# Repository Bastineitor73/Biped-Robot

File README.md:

# Contacto

Quieres ser parte de B1P0? Envía un correo a josespi@udec.cl, mariomedina@udec.cl, agarrido2018@udec.cl o ginostroza2020@udec.cl

# Contenidos
- [Proyecto B1P0](#proyecto-b1p0)
  * [Objetivo](#objetivo)
  * [Visiones](#visiones)
  * [Temas actuales](#temas-actuales)
  * [Diagrama Electrico](#diagrama-electrico)
- [Avances](#avances)
- [Invitacion Charla](#invitacion-charla)
- [Contacto](#contacto)

# Proyecto B1P0

Quieres ser parte de B1P0? Envía un correo a agarrido2018@udec.cl o a ginostroza2020@udec.cl

## Objetivo
"Crear un robot bípedo estable y escalable a lo largo del tiempo desarrollado por alumnos del DIE, capaz de desenvolverse en entornos industriales complejos, catástrofes naturales, inspecciones y escenarios de alto riesgo humano"

## Visiones

## Temas actuales
1.- Modelación física y desarrollo de un gemelo digital para entrenamiento y simulaciones

2.- Rediseño estructural del robot bípedo existente, mediante análisis de esfuerzos, estudio de materiales, mejoras en sistemas mecánicos y resistencia.

3.- Diseño e integración de una arquitectura de software basada en ROS/ROS2 para la comunicación entre CPU, microcontroladores, actuadores y usuario

4.- Diseño e implementación de un sistema de control remoto inalámbrico utilizando tecnologías RF, WiFi o Bluetooth.

5.- Diseño e implementación de un sistema de control adaptativo o predictivo para la estabilidad del robot bípedo

6.- Desarrollo de un sistema de estimación de estados mediante fusión de datos inerciales (IMU) y modelos dinámicos

7.- Implementación de un sistema de percepción visual y mapeo de entorno mediante cámara de profundidad

# Avance Actual

## Octubre 2025

https://github.com/user-attachments/assets/e0c73ede-dcd1-4829-920c-aed435cbe2b3

# Revisa nuestra Charla

https://www.canva.com/design/DAG2QE-IAb0/ETZ7DED0be4jHASCjCmeyw/view?utm_content=DAG2QE-IAb0&utm_campaign=designshare&utm_medium=link2&utm_source=uniquelinks&utlId=h5e711771e6

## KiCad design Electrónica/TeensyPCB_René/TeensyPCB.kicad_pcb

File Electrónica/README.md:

# Diagrama Electrico

# Lista de Dispositivos

## Microcontrolador Teensy 4.1

## SparkFun OpenLog Artemis

## Raspberry Pi 5, 16 GB RAM

## Cámara Intel RealSense D435i

## Batería Lipo
- 22.2V
- 6 celdas
- 5000 mAh

# Desarollo PCB's
Interacción de los componentes

## Monitor de bateria y Medidor de combustible
- Monitor MP2790
- Fuel Gauge MPF42795
- Comunicacion por I2C con librería "MP27XX.h"

- Placa accesoria para llave de paso MOS

- Placa accesoria UI Medidor de combustible

## Placa de alimentacion
- Conversor buck TPS54531 5V @25W
- Regulador lineal TLV757p 3V3 @3W

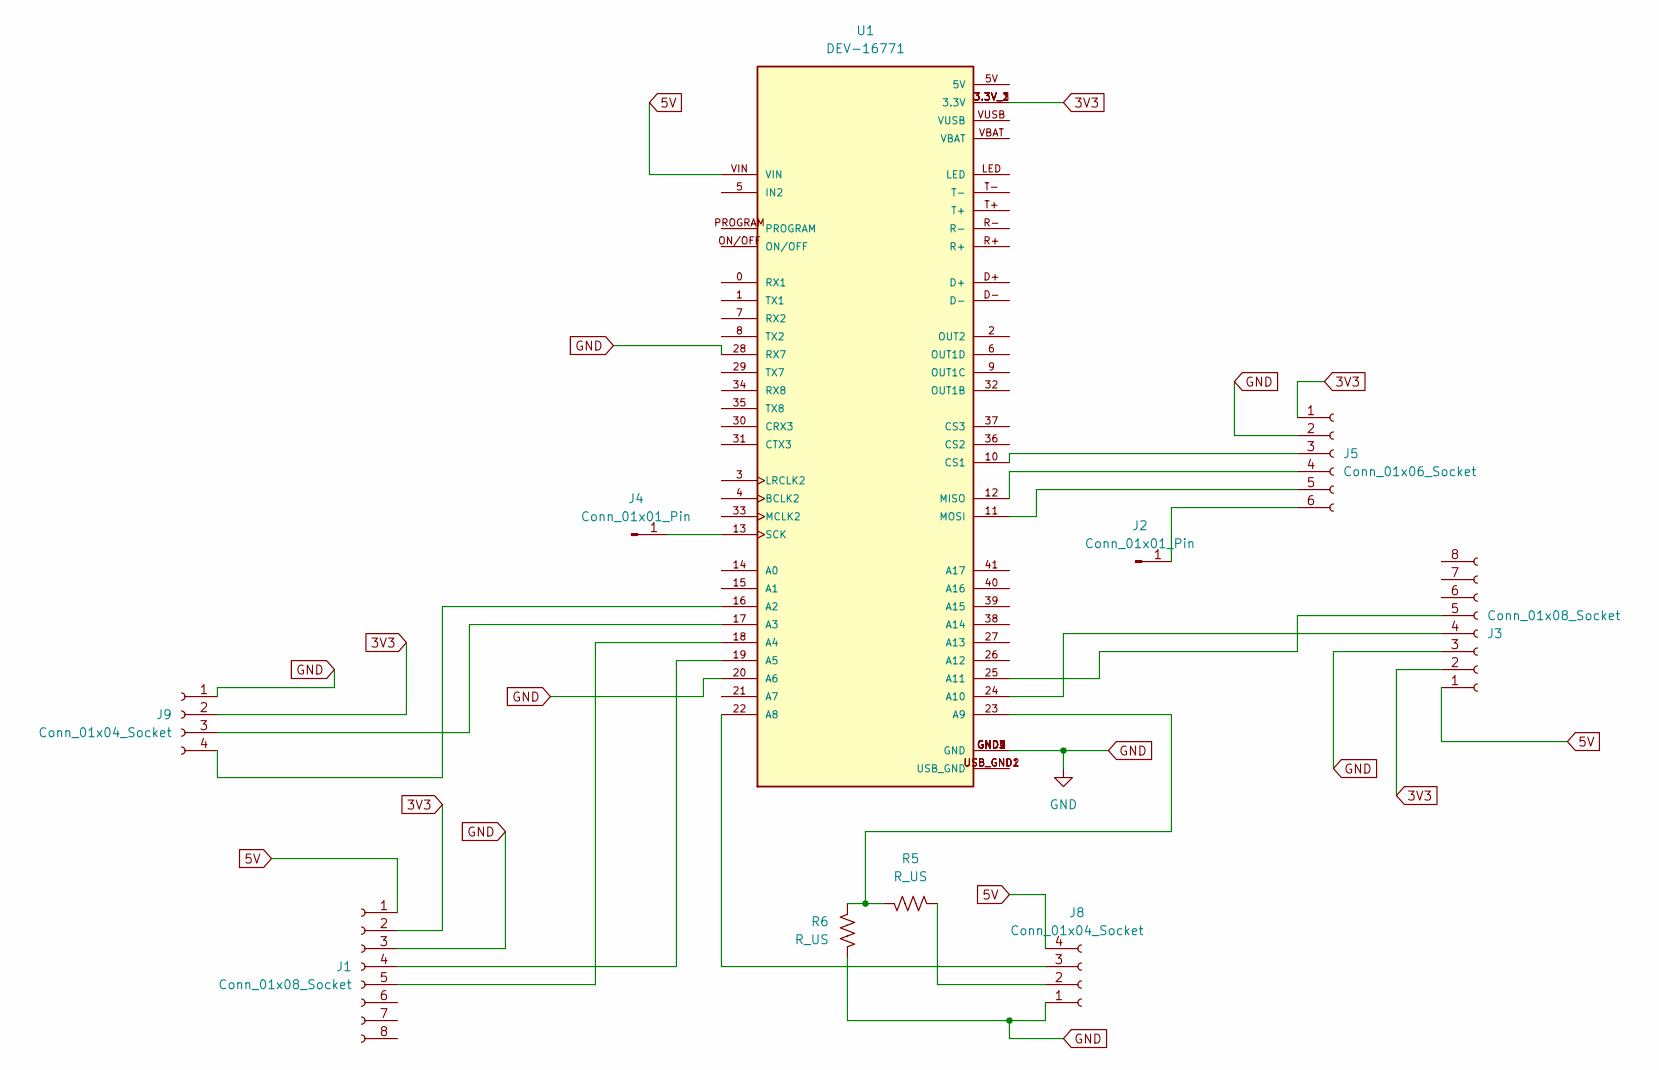
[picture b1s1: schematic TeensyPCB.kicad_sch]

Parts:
J1, J3: Conn_01x08_Socket; PinHeader_1x08_P2.54mm_Vertical
J2, J4: Conn_01x01_Pin; PinHeader_1x01_P2.54mm_Vertical
J5: Conn_01x06_Socket; PinHeader_1x06_P2.54mm_Vertical
J8, J9: Conn_01x04_Socket; PinHeader_1x04_P2.54mm_Vertical
R5, R6: R_US; R_Axial_DIN0207_L6.3mm_D2.5mm_P10.16mm_Horizontal
U1: DEV-16771; MODULE_DEV-16771; PARTREV 4.1

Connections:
3V3: J1.2, J3.2, J5.1, J9.2, U1.3.3V_1 (3.3V), U1.3.3V_2 (3.3V), U1.3.3V_3 (3.3V)
5V: J1.1, J3.1, J8.4, U1.VIN
GND: J1.3, J3.3, J5.2, J8.1, J9.1, R6.2, U1.20 (A6), U1.28 (RX7), U1.GND1 (GND), U1.GND2 (GND), U1.GND3 (GND), U1.GND4 (GND), U1.GND5 (GND)
unnamed: J1.4, U1.19 (A5)
unnamed: J1.5, U1.18 (A4)
unnamed: J2.1, J5.6
unnamed: J3.4, U1.24 (A10)
unnamed: J3.5, U1.25 (A11)
unnamed: J4.1, U1.13 (SCK)
unnamed: J5.3, U1.10 (CS1)
unnamed: J5.4, U1.12 (MISO)
unnamed: J5.5, U1.11 (MOSI)
unnamed: J8.2, R5.1
unnamed: J8.3, U1.22 (A8)
unnamed: J9.3, U1.17 (A3)
unnamed: J9.4, U1.16 (A2)
unnamed: R5.2, R6.1, U1.23 (A9)
unnamed: U1.USB_GND1 (USB_GND), U1.USB_GND2 (USB_GND)

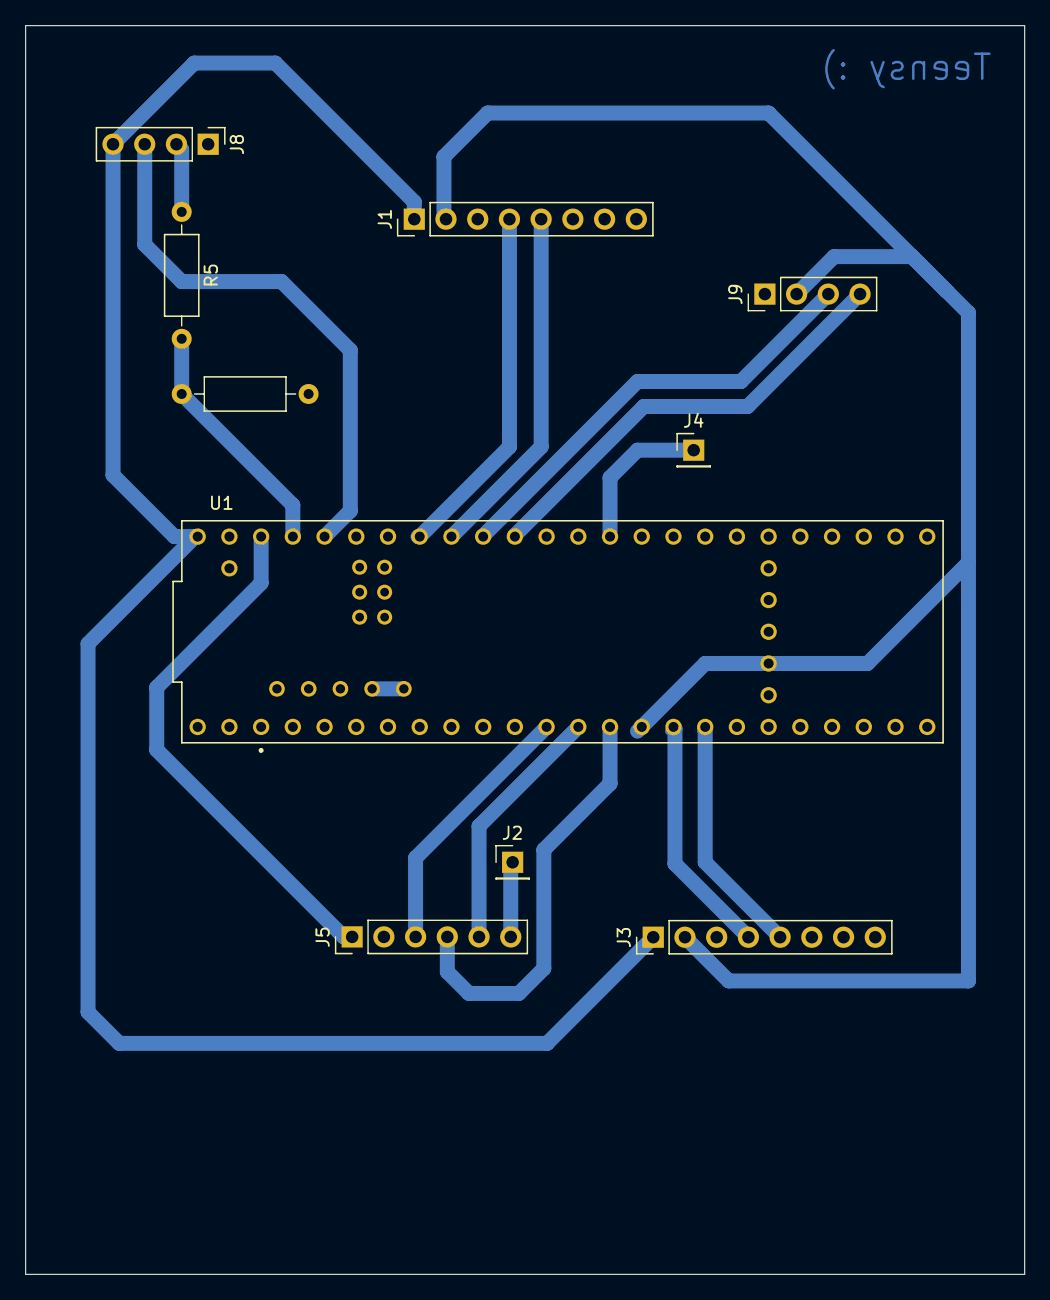
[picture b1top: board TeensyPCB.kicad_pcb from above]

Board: 2 copper layers, 80.0 x 100.0 mm, 10 parts (0 on the bottom side), 18 nets.

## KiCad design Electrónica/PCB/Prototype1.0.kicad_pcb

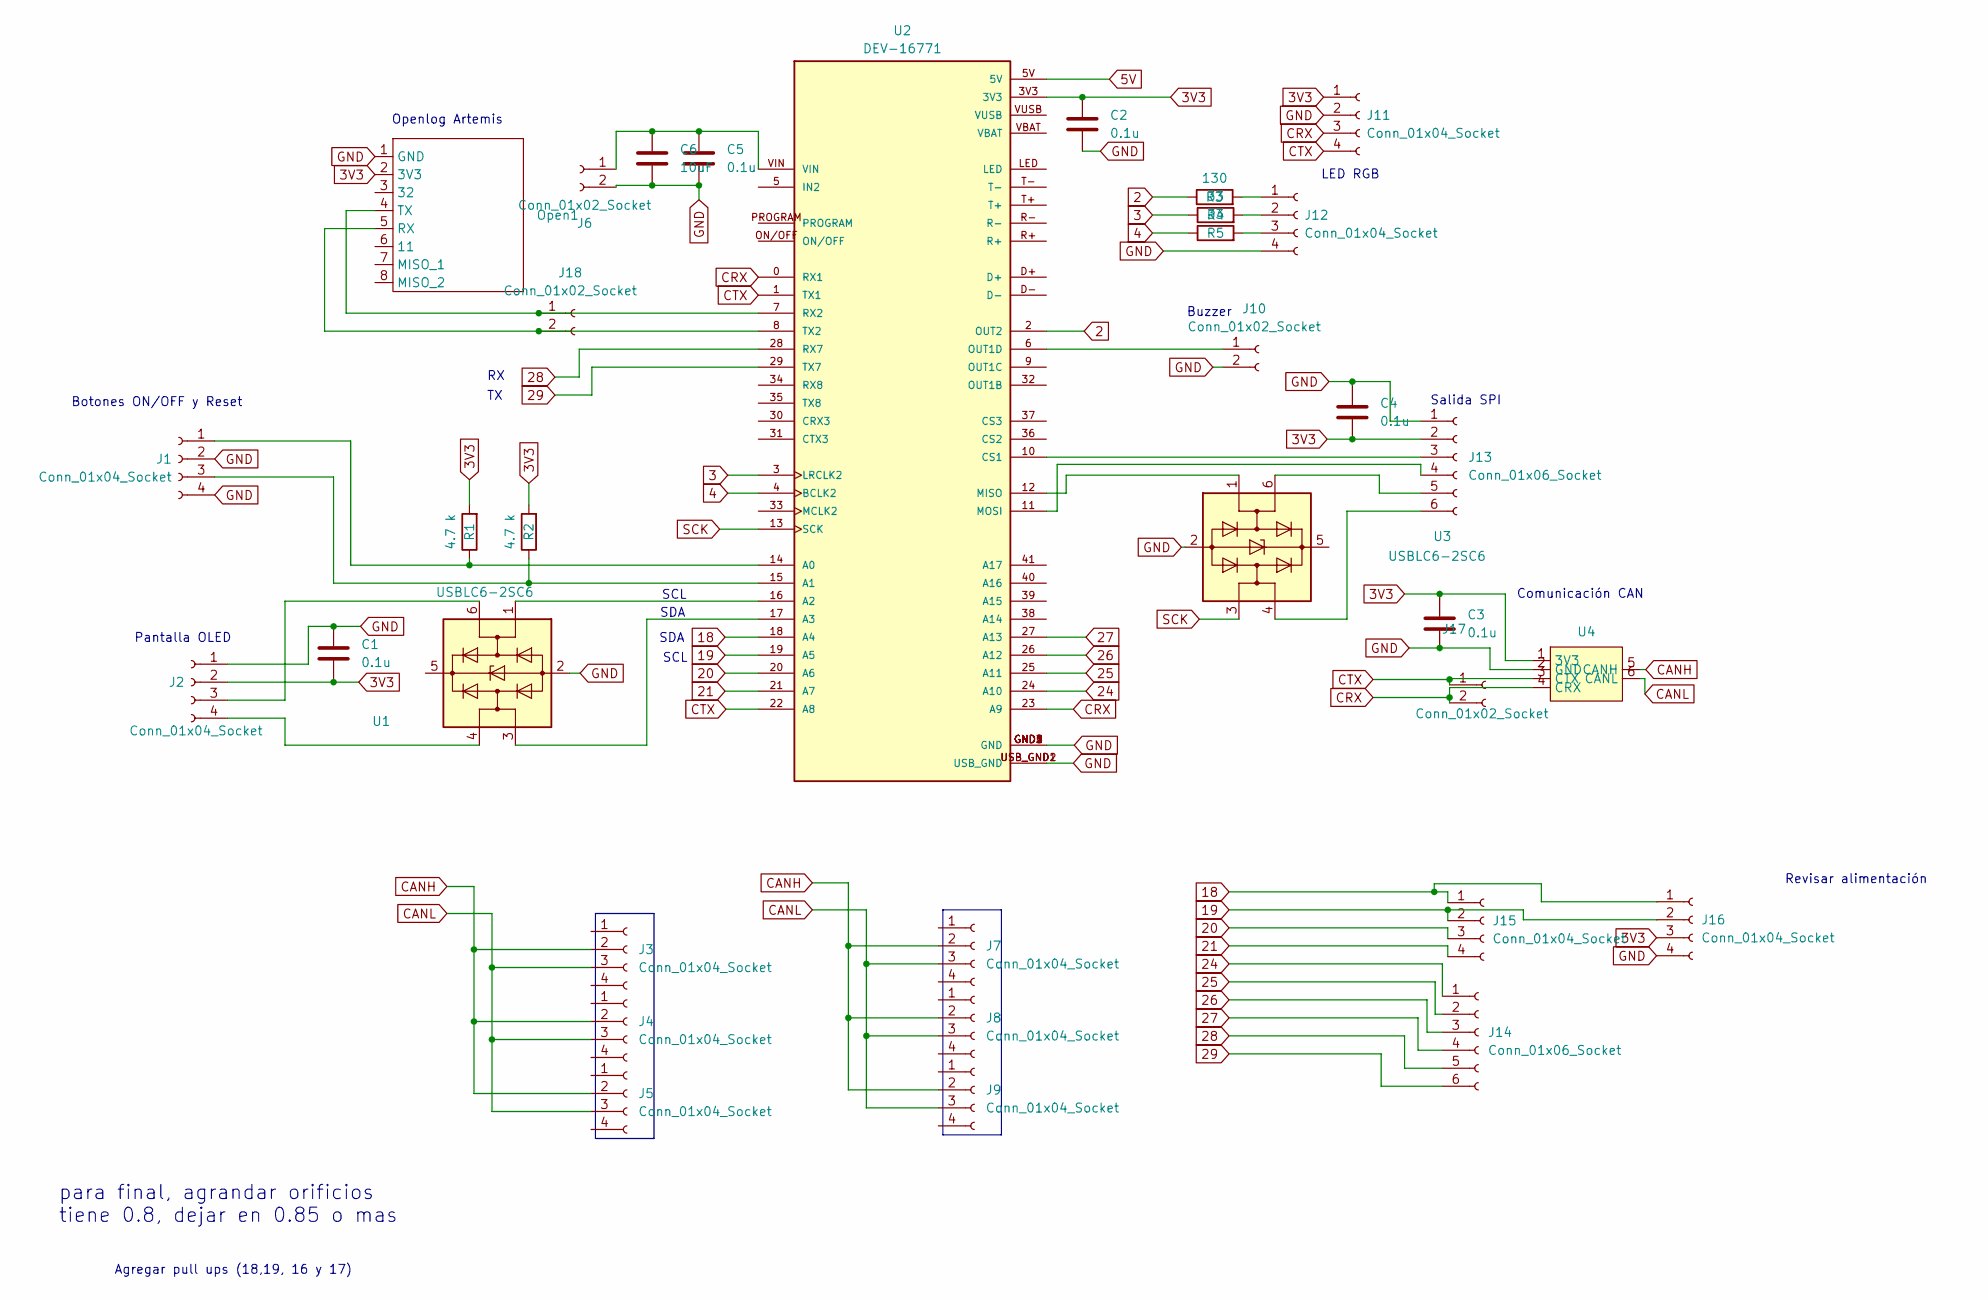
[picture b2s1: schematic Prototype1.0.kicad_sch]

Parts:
C1, C2, C3, C4, C5: 0.1u; C_0805_2012Metric_Pad1.18x1.45mm_HandSolder
C6: 10uF; C_0805_2012Metric_Pad1.18x1.45mm_HandSolder
J1, J2, J11, J12, J15, J16: Conn_01x04_Socket; PinSocket_1x04_P2.54mm_Vertical
J3, J4, J5, J7, J8, J9: Conn_01x04_Socket; JST_GH_SM04B-GHS-TB_1x04-1MP_P1.25mm_Horizontal
J6: Conn_01x02_Socket; TerminalBlock_Phoenix_MKDS-1,5-2-5.08_1x02_P5.08mm_Horizont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
J10, J17, J18: Conn_01x02_Socket; PinSocket_1x02_P2.54mm_Vertical
J13, J14: Conn_01x06_Socket; PinSocket_1x06_P2.54mm_Vertical
Open1: Openlog Artemis
R1, R2: 4.7 k; R_0805_2012Metric_Pad1.20x1.40mm_HandSolder
R3: 130; R_0805_2012Metric_Pad1.20x1.40mm_HandSolder
R4, R5: 33; R_0805_2012Metric_Pad1.20x1.40mm_HandSolder
U1, U3: USBLC6-2SC6; SOT-23-6
U2: DEV-16771; MODULE_DEV-16771; PARTREV 4.1
U4: ModuloCan

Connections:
2: R3.1, U2.2 (OUT2)
3: R4.1, U2.3 (LRCLK2)
3V3: C1.2, C2.1, C3.1, C4.2, J2.2, J11.1, J13.2, J16.3, Open1.2 (3V3), R1.2, R2.2, U2.3V3, U4.1 (3V3)
4: R5.1, U2.4 (BCLK2)
5V: U2.5V
18: J15.1, J16.1, U2.18 (A4)
19: J15.2, J16.2, U2.19 (A5)
20: J15.3, U2.20 (A6)
21: J15.4, U2.21 (A7)
24: J14.1, U2.24 (A10)
25: J14.2, U2.25 (A11)
26: J14.3, U2.26 (A12)
27: J14.4, U2.27 (A13)
28: J14.5, U2.28 (RX7)
29: J14.6, U2.29 (TX7)
CANH: J3.2, J4.2, J5.2, J7.2, J8.2, J9.2, U4.5 (CANH)
CANL: J3.3, J4.3, J5.3, J7.3, J8.3, J9.3, U4.6 (CANL)
CRX: J11.3, J17.2, U2.0 (RX1), U2.23 (A9), U4.4 (CRX)
CTX: J11.4, J17.1, U2.1 (TX1), U2.22 (A8), U4.3 (CTX)
GND: C1.1, C2.2, C3.2, C4.1, C5.2, C6.2, J1.2, J1.4, J2.1, J6.2, J10.2, J11.2, J12.4, J13.1, J16.4, Open1.1 (GND), U1.2 (GND), U2.GND1 (GND), U2.GND2 (GND), U2.GND3 (GND), U2.GND4 (GND), U2.GND5 (GND), U2.USB_GND1 (USB_GND), U2.USB_GND2 (USB_GND), U3.2 (GND), U4.2 (GND)
unnamed: J1.1, R1.1, U2.14 (A0)
unnamed: J1.3, R2.1, U2.15 (A1)
unnamed: J2.3, U1.6 (I/O1)
unnamed: J2.4, U1.4 (I/O2)
unnamed: C5.1, C6.1, J6.1, U2.VIN
unnamed: J10.1, U2.6 (OUT1D)
unnamed: J12.1, R3.2
unnamed: J12.2, R4.2
unnamed: J12.3, R5.2
unnamed: J13.3, U2.10 (CS1)
unnamed: J13.4, U2.11 (MOSI)
unnamed: J13.5, U3.6 (I/O1)
unnamed: J13.6, U3.4 (I/O2)
unnamed: J18.1, Open1.4 (TX), U2.7 (RX2)
unnamed: J18.2, Open1.5 (RX), U2.8 (TX2)
unnamed: U1.1 (I/O1), U2.16 (A2)
unnamed: U1.3 (I/O2), U2.17 (A3)
unnamed: U2.12 (MISO), U3.1 (I/O1)
SCK: U2.13 (SCK), U3.3 (I/O2)

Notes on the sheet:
Botones ON/OFF y Reset
SDA
Agregar pull ups (18,19, 16 y 17)
SCL
Buzzer
Comunicación CAN
Salida SPI
Revisar alimentación
LED RGB
para final, agrandar orificios tiene 0.8, dejar en 0.85 o mas
Openlog Artemis
Pantalla OLED

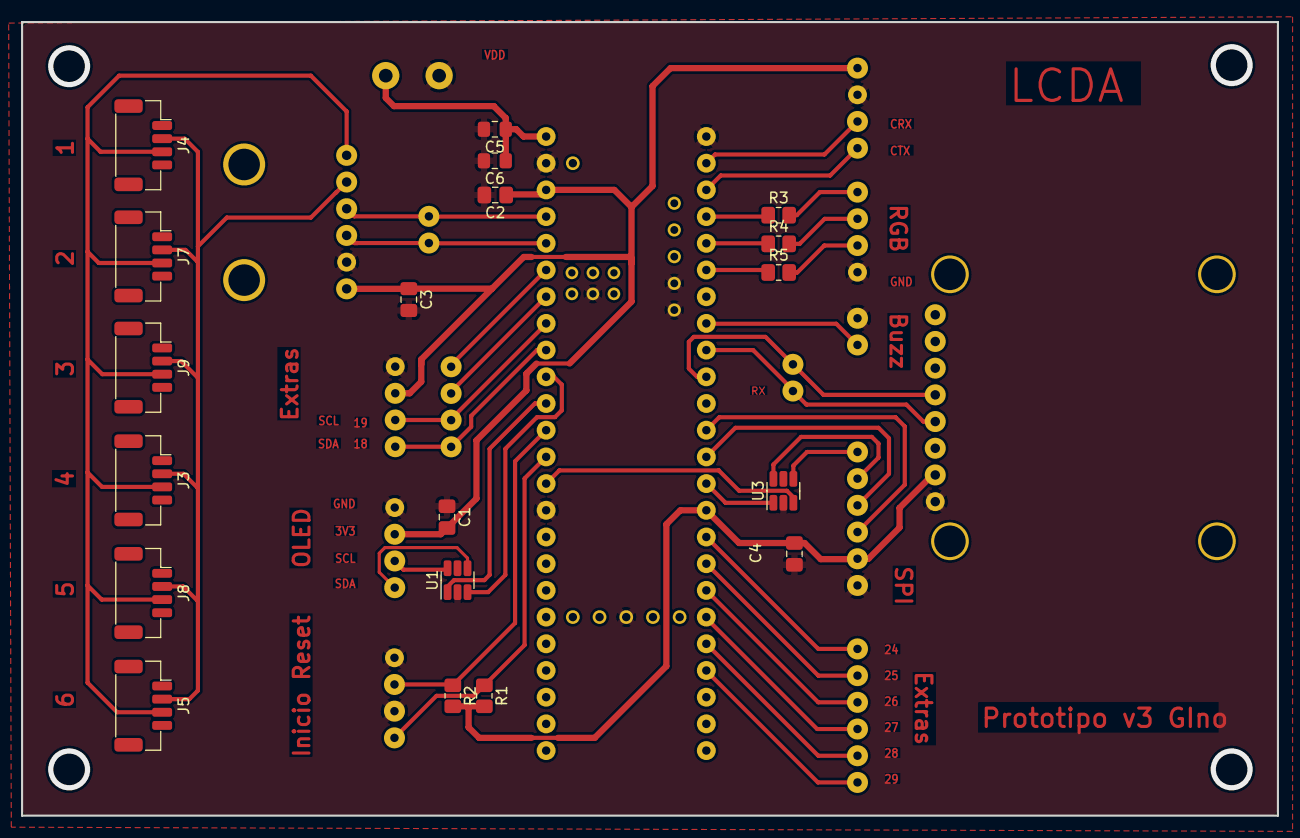
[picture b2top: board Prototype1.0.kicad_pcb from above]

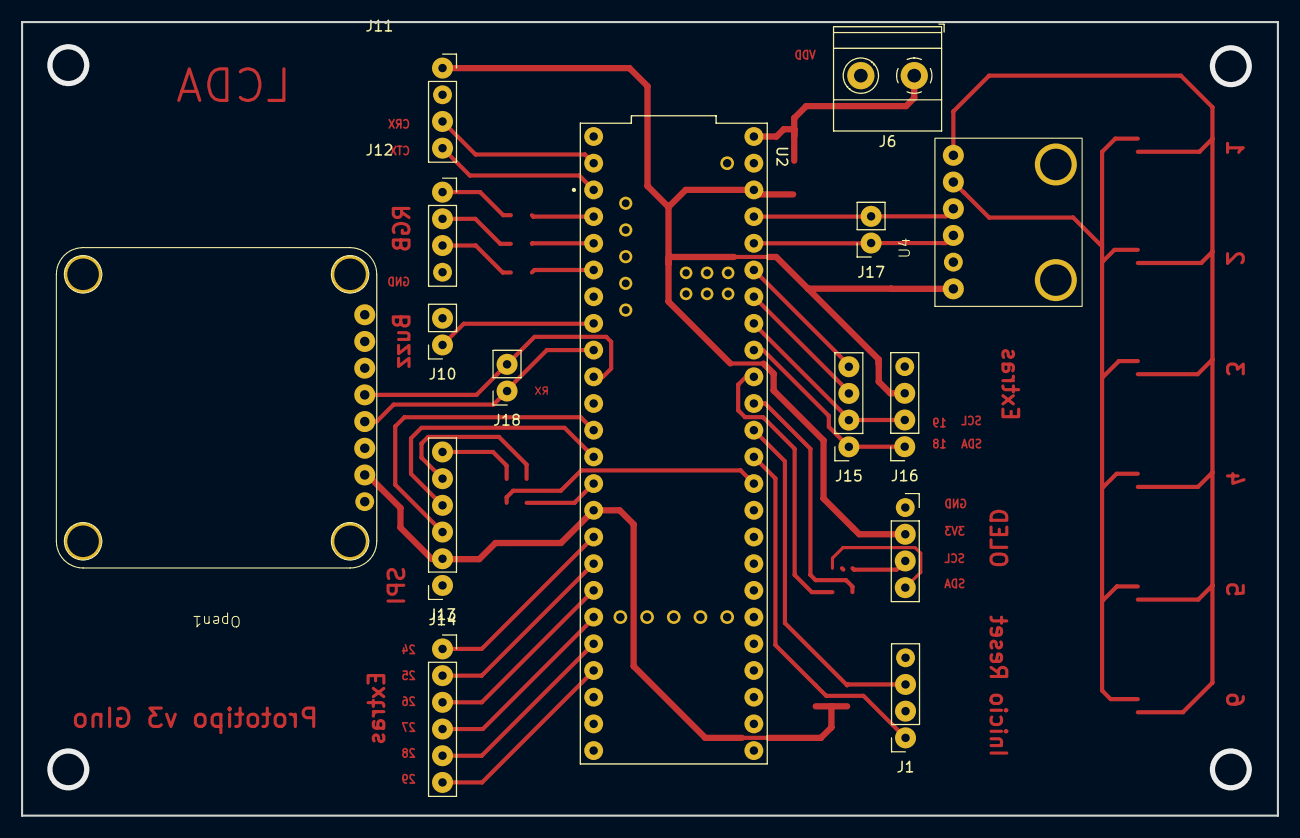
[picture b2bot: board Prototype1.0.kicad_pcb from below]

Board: 2 copper layers, 119.5 x 75.5 mm, 34 parts (15 on the bottom side), 38 nets.

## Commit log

2024-11-16 Create Papers
2025-04-05 Create aaaaa
2025-04-14 Create TeensyPCB_René
2025-04-14 Create aaa
2025-04-14 Rename Informe Final PELN Bastián.pdf to Actuadores Eléctricos Propioceptivos.pdf
2025-04-15 Agrego tabla de ensayos del motor
2025-07-23 Prototype1.0
2025-07-23 Create Fotos
2025-08-14 Esquema placas y software
2025-08-14 Rename PCB_MP2790png.png to PCB_MP2790.png
2025-08-14 Update README.md
    agregando placas alonso
2025-08-14 Subiendo libreria MP2790 alpha
    Para comunicarse con monitor de bateria
2025-08-14 resumen clase mp2790
2025-08-17 Actualizando rutina principal
2025-08-25 Adjust image dimensions in README.md
2025-08-25 Adjust image sizes in README.md
    Updated image dimensions in the README.
2025-08-25 Adjust image height in Avances section
    Updated image height in README for better display.
2025-08-25 Adjust image size in README
    Updated image dimensions in README.md for better display.
2025-08-26 Agregando carpeta librealsense dentro de Cámara
2025-08-26 Agregando carpeta librealsense como archivos normales
2025-09-11 Agrega rutina RTC y logger
2025-09-12 Create RoutineAugust
2025-09-12 Create Routine_08-2025
    kkjnk
2025-09-12 Unificacion en teensy
2025-10-13 Enhance Setup Odrive GUI documentation with new sections
    Added sections for Encoder, Control Mode, Interfaces, and Apply and Calibrate with corresponding images.
2025-10-13 Update Odrive GUI setup instructions for actuators
2025-10-13 Add controller parameters section to Odrive GUI setup
    Added section for controller parameters with image.
2025-10-28 Create Rutina_28-10
2025-10-28 Create mkjnk
2025-10-30 Add images to Proyecto B1P0 section
    Added images to the project section in README.
2025-10-30 Add electrical diagram and device list to README
2025-10-30 Create Docs
2025-10-30 Update README with current progress section
    Added a new section for current progress and a link.
2025-10-30 Add contact information to README
2025-10-30 Fix email list formatting in README.md
2025-11-17 Update event invitation details in README
2026-01-19 Add Final_Prototype file to PCB directory
2026-01-19 Create hola
